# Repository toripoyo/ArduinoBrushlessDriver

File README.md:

Arduino nano を使い、3相ブラシレスモーターを駆動する基板とプログラムです。

## 基板
/KiCad ディレクトリ下に、KiCadプロジェクト一式が保存されています。  
　回路図：Inverter.pdf  
　部品表：PartsList.xlsx  

## 制御プログラム
ArduinoBrushlessDriver下に、Arduinoプロジェクト一式が保存されています。

## 基板の動作
1. 3相ブラシレスモーターをUVW出力端子に接続し、基板に12Vを供給します
1. ボリューム（RV1）を最小位置から1/4ほどの位置にします
1. SW1を押すと、モーターが強制回転され、その後センサレス駆動がはじまります
1. RV1を調整すると、出力電圧が調整でき、回転速度を変えることができます

## モーターに合わせた調整
* 強制回転の際にうまく回らない場合は、RV1を回し、印可電圧を上げて試してみてください。（上げすぎに注意）
* 強制回転を終了する回転数を調整したい場合は、プログラム179行目の定数の値を書き換えてください

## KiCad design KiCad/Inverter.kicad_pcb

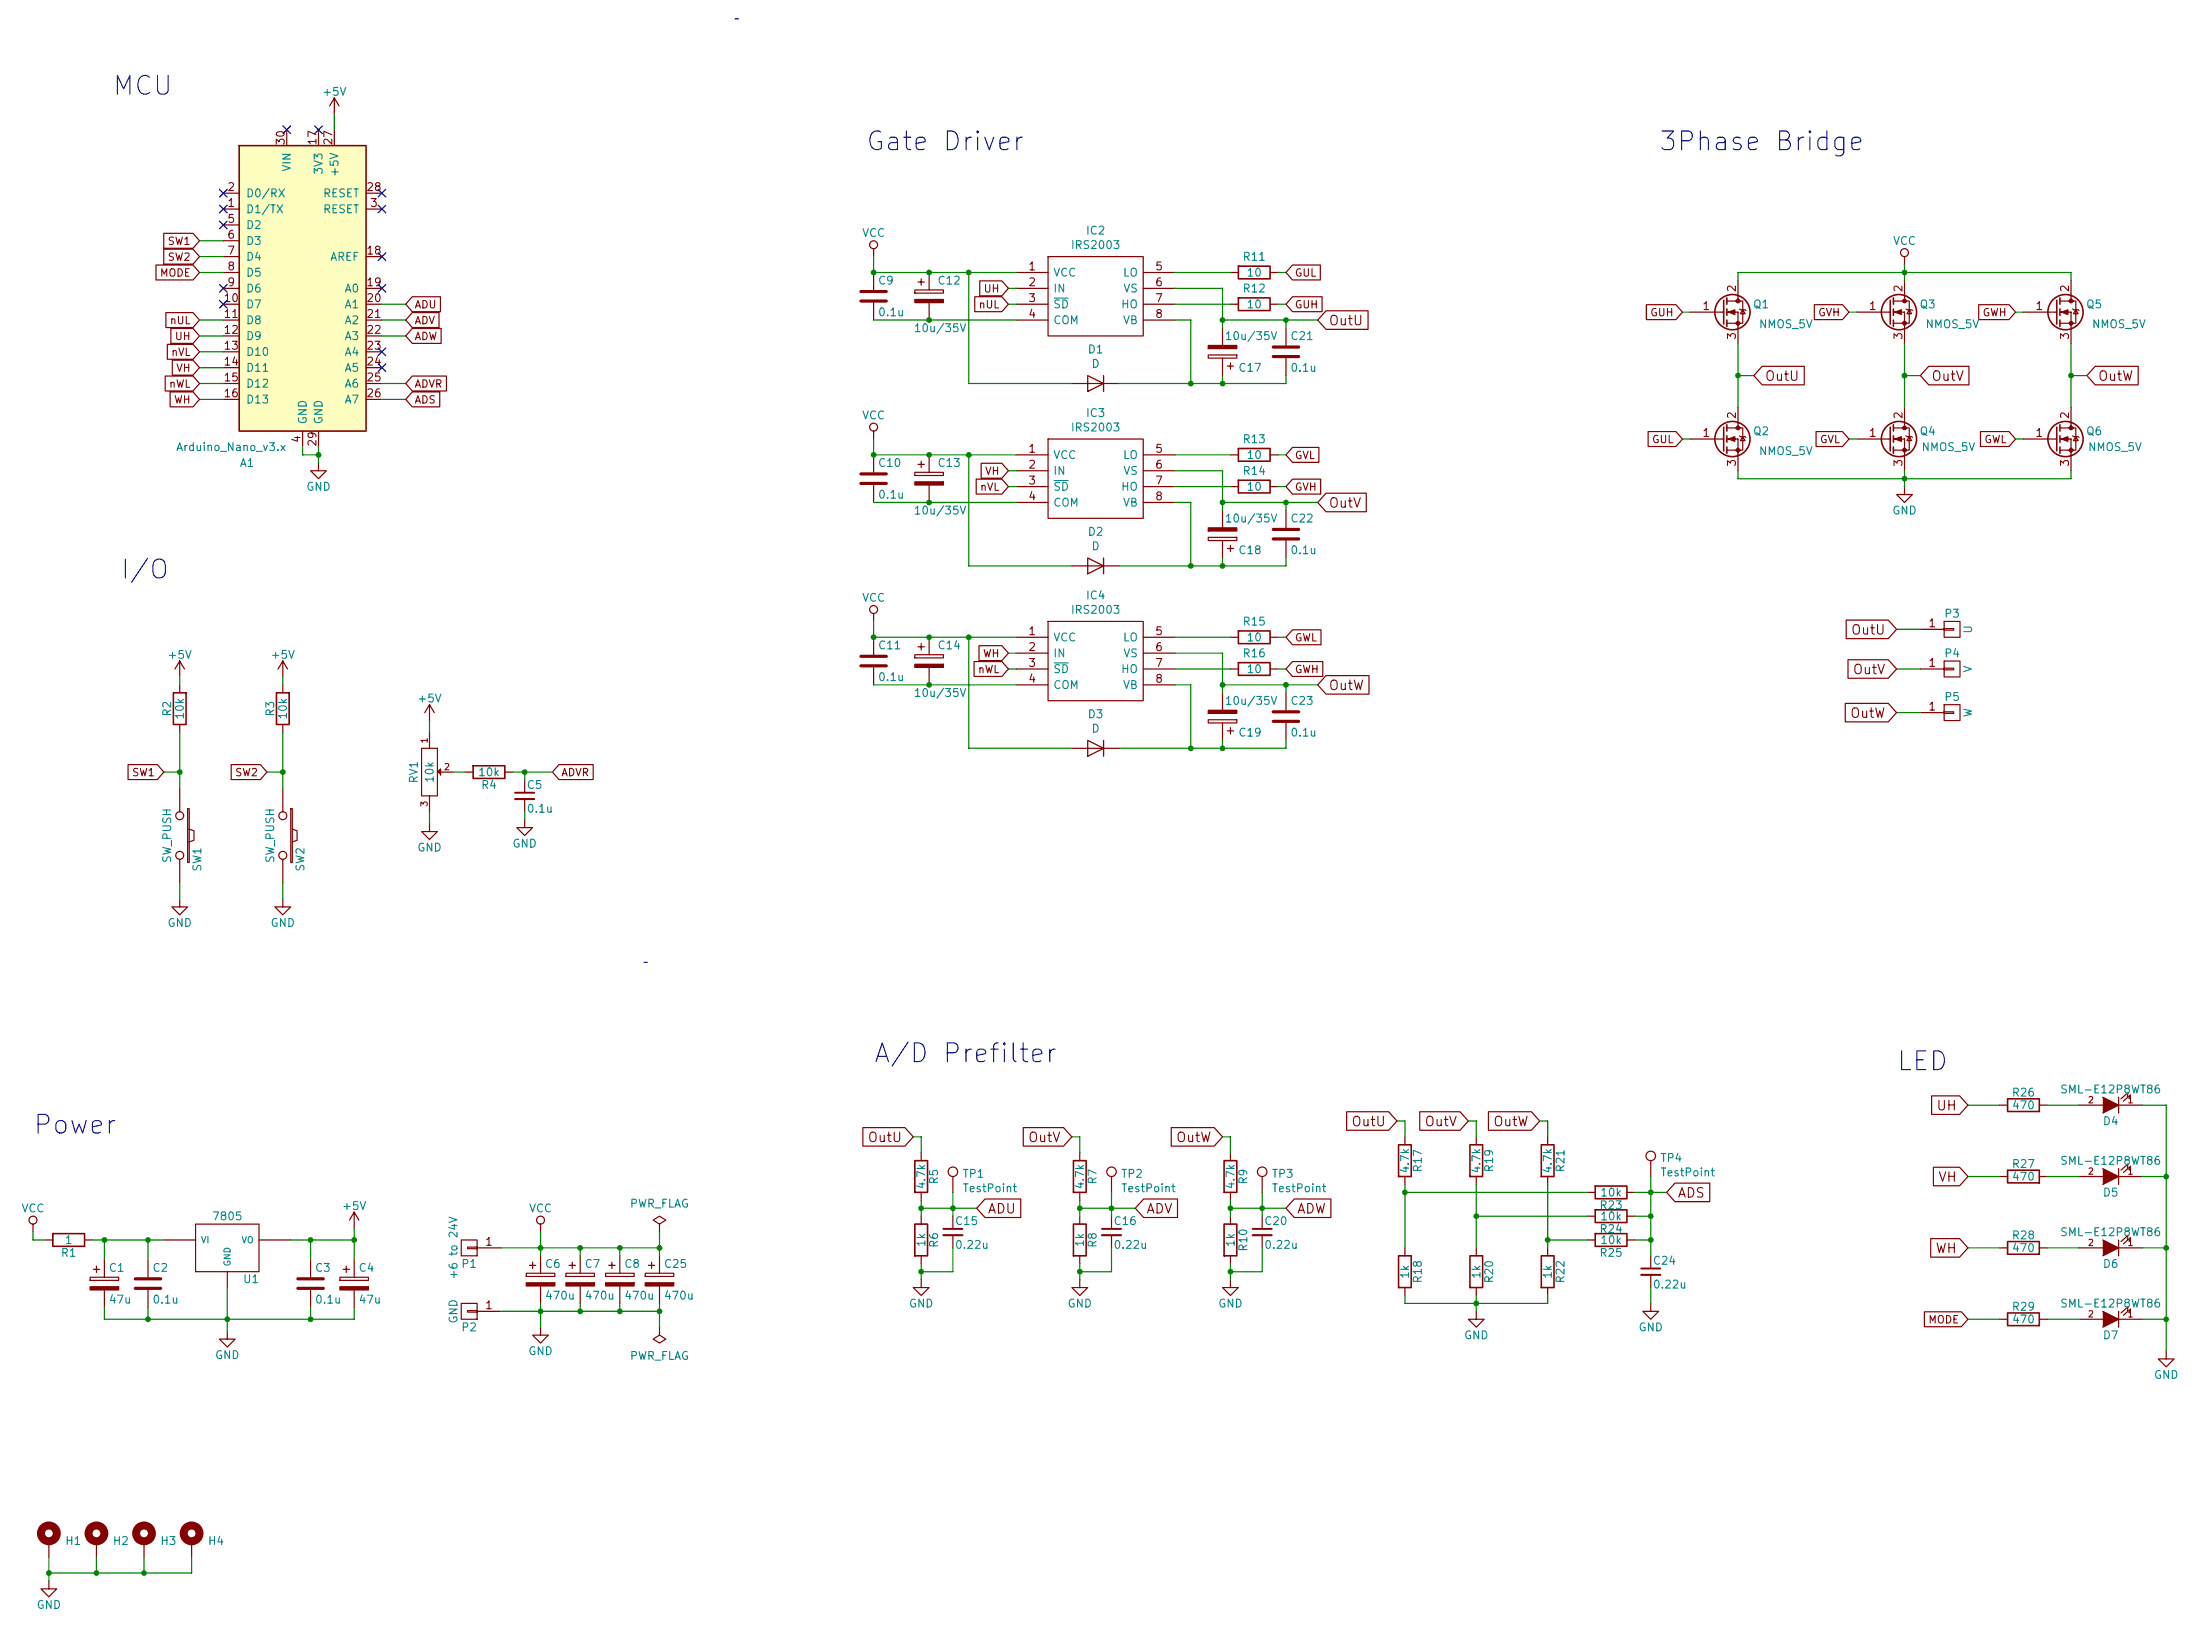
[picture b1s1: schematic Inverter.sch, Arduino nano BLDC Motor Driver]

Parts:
A1: Arduino_Nano_v3.x; Arduino_Nano
C1, C4: 47u; CP_Radial_D5.0mm_P2.50mm
C2, C3, C5, C9, C10, C11, C21, C22, C23: 0.1u; C_0603_1608Metric_Pad1.05x0.95mm_HandSolder
C6, C7, C8, C25: 470u; CP_Radial_D12.5mm_P5.00mm
C12, C13, C14, C17, C18, C19: 10u/35V; CP_Radial_D5.0mm_P2.00mm
C15, C16, C20, C24: 0.22u; C_0603_1608Metric_Pad1.05x0.95mm_HandSolder
D1, D2, D3: D; D_SOD-123
D4, D5, D6, D7: SML-E12P8WT86; LED_0603_1608Metric_Pad1.05x0.95mm_HandSolder
H1, H2, H3, H4: MountingHole_Pad; MountingHole_3.2mm_M3_Pad
IC2, IC3, IC4: IRS2003; SOIC127P600X175-8N; Manufacturer_Part_Number IR2104STRPBF
P1: +6 to 24V; SolderWirePad_1x01_SMD_5x10mm
P2: GND; SolderWirePad_1x01_SMD_5x10mm
P3: U; SolderWirePad_1x01_SMD_5x10mm
P4: V; SolderWirePad_1x01_SMD_5x10mm
P5: W; SolderWirePad_1x01_SMD_5x10mm
Q1, Q2, Q3, Q4, Q5, Q6: NMOS_5V; TO-252-3_TabPin2
R1: 1; R_Axial_DIN0309_L9.0mm_D3.2mm_P2.54mm_Vertical
R2, R3, R4, R23, R24, R25: 10k; R_0603_1608Metric_Pad1.05x0.95mm_HandSolder
R5, R7, R9, R17, R19, R21: 4.7k; R_0603_1608Metric_Pad1.05x0.95mm_HandSolder
R6, R8, R10, R18, R20, R22: 1k; R_0603_1608Metric_Pad1.05x0.95mm_HandSolder
R11, R12, R13, R14, R15, R16: 10; R_0603_1608Metric_Pad1.05x0.95mm_HandSolder
R26, R27, R28, R29: 470; R_0603_1608Metric_Pad1.05x0.95mm_HandSolder
RV1: 10k; Potentiometer_Alps_RK09K_Single_Vertical
SW1, SW2: SW_PUSH; SW_PUSH_6mm
TP1, TP2, TP3, TP4: TestPoint; TestPoint_THTPad_D1.0mm_Drill0.5mm
U1: 7805; TO-252-3_TabPin2

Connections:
+5V: A1.27 (+5V), C3.1, C4.1, R2.2, R3.2, RV1.1, U1.3 (VO)
ADS: A1.26 (A7), C24.1, R23.1, R24.1, R25.1, TP4.1
ADU: A1.20 (A1), C15.1, R5.2, R6.1, TP1.1
ADV: A1.21 (A2), C16.1, R7.2, R8.1, TP2.1
ADVR: A1.25 (A6), C5.1, R4.1
ADW: A1.22 (A3), C20.1, R9.2, R10.1, TP3.1
GND: A1.4 (GND), A1.29 (GND), C1.2, C2.2, C3.2, C4.2, C5.2, C6.2, C7.2, C8.2, C15.2, C16.2, C20.2, C24.2, C25.2, D4.1 (K), D5.1 (K), D6.1 (K), D7.1 (K), H1.1, H2.1, H3.1, H4.1, P2.1, Q2.3 (S), Q4.3 (S), Q6.3 (S), R6.2, R8.2, R10.2, R18.2, R20.2, R22.2, RV1.3, SW1.2, SW2.2, U1.2 (GND)
GUH: Q1.1 (G), R12.1
GUL: Q2.1 (G), R11.1
GVH: Q3.1 (G), R14.1
GVL: Q4.1 (G), R13.1
GWH: Q5.1 (G), R16.1
GWL: Q6.1 (G), R15.1
MODE: A1.8 (D5), R29.1
unnamed: C1.1, C2.1, R1.1, U1.1 (VI)
unnamed: C10.2, C13.2, IC3.4 (COM)
unnamed: C11.2, C14.2, IC4.4 (COM)
unnamed: C9.2, C12.2, IC2.4 (COM)
unnamed: C17.1, C21.2, D1.1 (K), IC2.8 (VB)
unnamed: C18.1, C22.2, D2.1 (K), IC3.8 (VB)
unnamed: C19.1, C23.2, D3.1 (K), IC4.8 (VB)
unnamed: D4.2 (A), R26.2
unnamed: D5.2 (A), R27.2
unnamed: D6.2 (A), R28.2
unnamed: D7.2 (A), R29.2
unnamed: IC2.5 (LO), R11.2
unnamed: IC2.7 (HO), R12.2
unnamed: IC3.5 (LO), R13.2
unnamed: IC3.7 (HO), R14.2
unnamed: IC4.5 (LO), R15.2
unnamed: IC4.7 (HO), R16.2
unnamed: R4.2, RV1.2
unnamed: R17.2, R18.1, R23.2
unnamed: R19.2, R20.1, R24.2
unnamed: R21.2, R22.1, R25.2
OutU: C17.2, C21.1, IC2.6 (VS), P3.1, Q1.3 (S), Q2.2 (D), R5.1, R17.1
OutV: C18.2, C22.1, IC3.6 (VS), P4.1, Q3.3 (S), Q4.2 (D), R7.1, R19.1
OutW: C19.2, C23.1, IC4.6 (VS), P5.1, Q5.3 (S), Q6.2 (D), R9.1, R21.1
SW1: A1.6 (D3), R2.1, SW1.1
SW2: A1.7 (D4), R3.1, SW2.1
UH: A1.12 (D9), IC2.2 (IN), R26.1
VCC: C6.1, C7.1, C8.1, C9.1, C10.1, C11.1, C12.1, C13.1, C14.1, C25.1, D1.2 (A), D2.2 (A), D3.2 (A), IC2.1 (VCC), IC3.1 (VCC), IC4.1 (VCC), P1.1, Q1.2 (D), Q3.2 (D), Q5.2 (D), R1.2
VH: A1.14 (D11), IC3.2 (IN), R27.1
WH: A1.16 (D13), IC4.2 (IN), R28.1
nUL: A1.11 (D8), IC2.3 (~SD)
nVL: A1.13 (D10), IC3.3 (~SD)
nWL: A1.15 (D12), IC4.3 (~SD)

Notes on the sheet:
MCU
A/D Prefilter
Power
3Phase Bridge
LED
I/O
Gate Driver

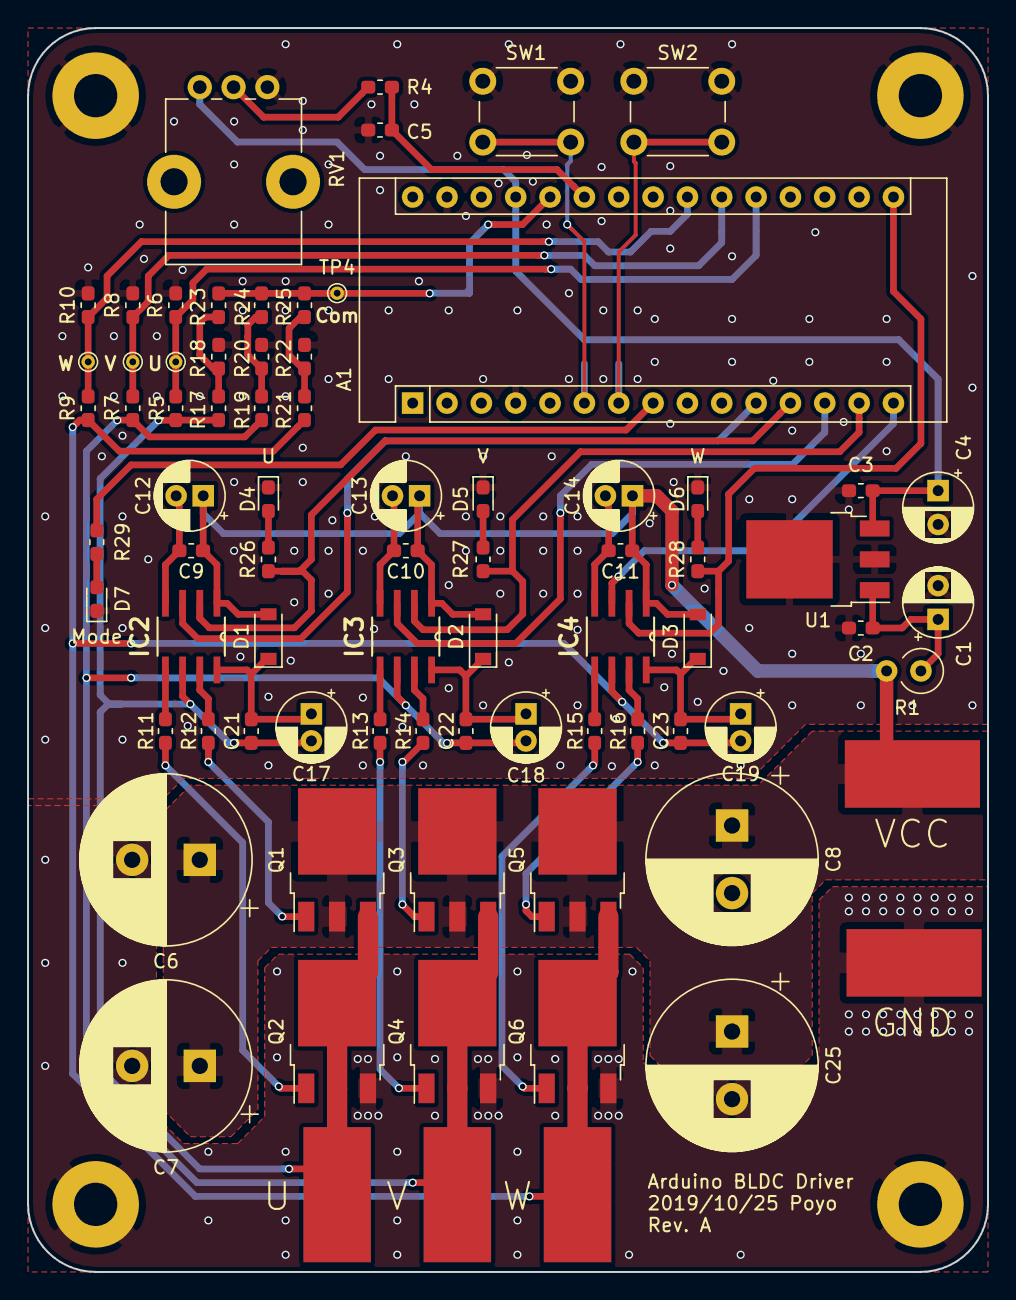
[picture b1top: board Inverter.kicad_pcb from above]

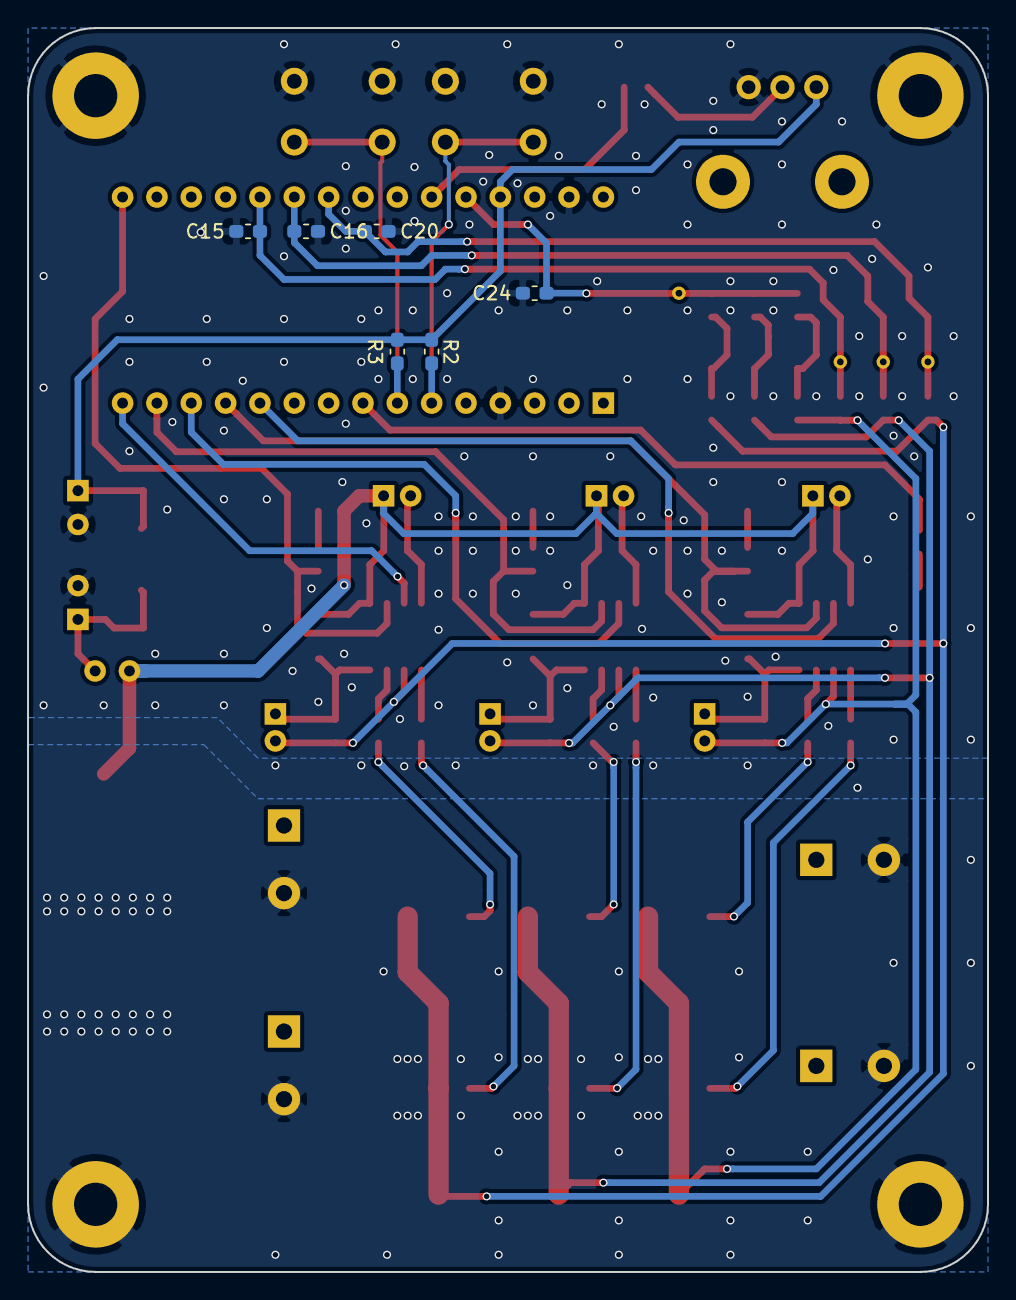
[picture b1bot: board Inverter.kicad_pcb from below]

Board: 2 copper layers, 71.0 x 92.0 mm, 88 parts (6 on the bottom side), 47 nets.

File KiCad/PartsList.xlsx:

Reference | Value | Footprint | Datasheet | Description | Manufacturer_Name | Manufacturer_Part_Number
A1 | Arduino_Nano_v3.x | Module:Arduino_Nano | http://www.mouser.com/pdfdocs/Gravitech_Arduino_Nano3_0.pdf
C1 | 47u | Capacitor_THT:CP_Radial_D5.0mm_P2.50mm
C10 | 0.1u | Capacitor_SMD:C_0603_1608Metric_Pad1.05x0.95mm_HandSolder
C11 | 0.1u | Capacitor_SMD:C_0603_1608Metric_Pad1.05x0.95mm_HandSolder
C12 | 10u/35V | Capacitor_THT:CP_Radial_D5.0mm_P2.00mm | ~
C13 | 10u/35V | Capacitor_THT:CP_Radial_D5.0mm_P2.00mm | ~
C14 | 10u/35V | Capacitor_THT:CP_Radial_D5.0mm_P2.00mm | ~
C15 | 0.22u | Capacitor_SMD:C_0603_1608Metric_Pad1.05x0.95mm_HandSolder
C16 | 0.22u | Capacitor_SMD:C_0603_1608Metric_Pad1.05x0.95mm_HandSolder
C17 | 10u/35V | Capacitor_THT:CP_Radial_D5.0mm_P2.00mm | ~
C18 | 10u/35V | Capacitor_THT:CP_Radial_D5.0mm_P2.00mm | ~
C19 | 10u/35V | Capacitor_THT:CP_Radial_D5.0mm_P2.00mm | ~
C2 | 0.1u | Capacitor_SMD:C_0603_1608Metric_Pad1.05x0.95mm_HandSolder
C20 | 0.22u | Capacitor_SMD:C_0603_1608Metric_Pad1.05x0.95mm_HandSolder
C21 | 0.1u | Capacitor_SMD:C_0603_1608Metric_Pad1.05x0.95mm_HandSolder
C22 | 0.1u | Capacitor_SMD:C_0603_1608Metric_Pad1.05x0.95mm_HandSolder
C23 | 0.1u | Capacitor_SMD:C_0603_1608Metric_Pad1.05x0.95mm_HandSolder
C24 | 0.22u | Capacitor_SMD:C_0603_1608Metric_Pad1.05x0.95mm_HandSolder
C25 | 470u | Capacitor_THT:CP_Radial_D12.5mm_P5.00mm
C3 | 0.1u | Capacitor_SMD:C_0603_1608Metric_Pad1.05x0.95mm_HandSolder
C4 | 47u | Capacitor_THT:CP_Radial_D5.0mm_P2.50mm
C5 | 0.1u | Capacitor_SMD:C_0603_1608Metric_Pad1.05x0.95mm_HandSolder
C6 | 470u | Capacitor_THT:CP_Radial_D12.5mm_P5.00mm
C7 | 470u | Capacitor_THT:CP_Radial_D12.5mm_P5.00mm
C8 | 470u | Capacitor_THT:CP_Radial_D12.5mm_P5.00mm
C9 | 0.1u | Capacitor_SMD:C_0603_1608Metric_Pad1.05x0.95mm_HandSolder
D1 | D | Diode_SMD:D_SOD-123 | ~
D2 | D | Diode_SMD:D_SOD-123 | ~
D3 | D | Diode_SMD:D_SOD-123 | ~
D4 | SML-E12P8WT86 | LED_SMD:LED_0603_1608Metric_Pad1.05x0.95mm_HandSolder
D5 | SML-E12P8WT86 | LED_SMD:LED_0603_1608Metric_Pad1.05x0.95mm_HandSolder
D6 | SML-E12P8WT86 | LED_SMD:LED_0603_1608Metric_Pad1.05x0.95mm_HandSolder
D7 | SML-E12P8WT86 | LED_SMD:LED_0603_1608Metric_Pad1.05x0.95mm_HandSolder
H1 | MountingHole_Pad | MountingHole:MountingHole_3.2mm_M3_Pad | ~
H2 | MountingHole_Pad | MountingHole:MountingHole_3.2mm_M3_Pad | ~
H3 | MountingHole_Pad | MountingHole:MountingHole_3.2mm_M3_Pad | ~
H4 | MountingHole_Pad | MountingHole:MountingHole_3.2mm_M3_Pad | ~
IC2 | IRS2003 | SamacSys_Parts:SOIC127P600X175-8N |  | HALF-BRIDGE DRIVER | International Rectifier | IR2104STRPBF
IC3 | IRS2003 | SamacSys_Parts:SOIC127P600X175-8N |  | HALF-BRIDGE DRIVER | International Rectifier | IR2104STRPBF
IC4 | IRS2003 | SamacSys_Parts:SOIC127P600X175-8N |  | HALF-BRIDGE DRIVER | International Rectifier | IR2104STRPBF
P1 | +6 to 24V | Connector_Wire:SolderWirePad_1x01_SMD_5x10mm
P2 | GND | Connector_Wire:SolderWirePad_1x01_SMD_5x10mm
P3 | U | Connector_Wire:SolderWirePad_1x01_SMD_5x10mm
P4 | V | Connector_Wire:SolderWirePad_1x01_SMD_5x10mm
P5 | W | Connector_Wire:SolderWirePad_1x01_SMD_5x10mm
Q1 | NMOS_5V | Package_TO_SOT_SMD:TO-252-3_TabPin2
Q2 | NMOS_5V | Package_TO_SOT_SMD:TO-252-3_TabPin2
Q3 | NMOS_5V | Package_TO_SOT_SMD:TO-252-3_TabPin2
Q4 | NMOS_5V | Package_TO_SOT_SMD:TO-252-3_TabPin2
Q5 | NMOS_5V | Package_TO_SOT_SMD:TO-252-3_TabPin2
Q6 | NMOS_5V | Package_TO_SOT_SMD:TO-252-3_TabPin2
R1 | 1 | Resistor_THT:R_Axial_DIN0309_L9.0mm_D3.2mm_P2.54mm_Vertical
R10 | 1k | Resistor_SMD:R_0603_1608Metric_Pad1.05x0.95mm_HandSolder
R11 | 10 | Resistor_SMD:R_0603_1608Metric_Pad1.05x0.95mm_HandSolder
R12 | 10 | Resistor_SMD:R_0603_1608Metric_Pad1.05x0.95mm_HandSolder
R13 | 10 | Resistor_SMD:R_0603_1608Metric_Pad1.05x0.95mm_HandSolder
R14 | 10 | Resistor_SMD:R_0603_1608Metric_Pad1.05x0.95mm_HandSolder
R15 | 10 | Resistor_SMD:R_0603_1608Metric_Pad1.05x0.95mm_HandSolder
R16 | 10 | Resistor_SMD:R_0603_1608Metric_Pad1.05x0.95mm_HandSolder
R17 | 4.7k | Resistor_SMD:R_0603_1608Metric_Pad1.05x0.95mm_HandSolder
R18 | 1k | Resistor_SMD:R_0603_1608Metric_Pad1.05x0.95mm_HandSolder
R19 | 4.7k | Resistor_SMD:R_0603_1608Metric_Pad1.05x0.95mm_HandSolder
R2 | 10k | Resistor_SMD:R_0603_1608Metric_Pad1.05x0.95mm_HandSolder
R20 | 1k | Resistor_SMD:R_0603_1608Metric_Pad1.05x0.95mm_HandSolder
R21 | 4.7k | Resistor_SMD:R_0603_1608Metric_Pad1.05x0.95mm_HandSolder
R22 | 1k | Resistor_SMD:R_0603_1608Metric_Pad1.05x0.95mm_HandSolder
R23 | 10k | Resistor_SMD:R_0603_1608Metric_Pad1.05x0.95mm_HandSolder
R24 | 10k | Resistor_SMD:R_0603_1608Metric_Pad1.05x0.95mm_HandSolder
R25 | 10k | Resistor_SMD:R_0603_1608Metric_Pad1.05x0.95mm_HandSolder
R26 | 470 | Resistor_SMD:R_0603_1608Metric_Pad1.05x0.95mm_HandSolder
R27 | 470 | Resistor_SMD:R_0603_1608Metric_Pad1.05x0.95mm_HandSolder
R28 | 470 | Resistor_SMD:R_0603_1608Metric_Pad1.05x0.95mm_HandSolder
R29 | 470 | Resistor_SMD:R_0603_1608Metric_Pad1.05x0.95mm_HandSolder
R3 | 10k | Resistor_SMD:R_0603_1608Metric_Pad1.05x0.95mm_HandSolder
R4 | 10k | Resistor_SMD:R_0603_1608Metric_Pad1.05x0.95mm_HandSolder
R5 | 4.7k | Resistor_SMD:R_0603_1608Metric_Pad1.05x0.95mm_HandSolder
R6 | 1k | Resistor_SMD:R_0603_1608Metric_Pad1.05x0.95mm_HandSolder
R7 | 4.7k | Resistor_SMD:R_0603_1608Metric_Pad1.05x0.95mm_HandSolder
R8 | 1k | Resistor_SMD:R_0603_1608Metric_Pad1.05x0.95mm_HandSolder
R9 | 4.7k | Resistor_SMD:R_0603_1608Metric_Pad1.05x0.95mm_HandSolder
RV1 | 10k | Potentiometer_THT:Potentiometer_Alps_RK09K_Single_Vertical
SW1 | SW_PUSH | Button_Switch_THT:SW_PUSH_6mm
SW2 | SW_PUSH | Button_Switch_THT:SW_PUSH_6mm
TP1 | TestPoint | TestPoint:TestPoint_THTPad_D1.0mm_Drill0.5mm | ~
TP2 | TestPoint | TestPoint:TestPoint_THTPad_D1.0mm_Drill0.5mm | ~
TP3 | TestPoint | TestPoint:TestPoint_THTPad_D1.0mm_Drill0.5mm | ~
TP4 | TestPoint | TestPoint:TestPoint_THTPad_D1.0mm_Drill0.5mm | ~
U1 | 7805 | Package_TO_SOT_SMD:TO-252-3_TabPin2

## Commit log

2019-12-30 公開用に整理
